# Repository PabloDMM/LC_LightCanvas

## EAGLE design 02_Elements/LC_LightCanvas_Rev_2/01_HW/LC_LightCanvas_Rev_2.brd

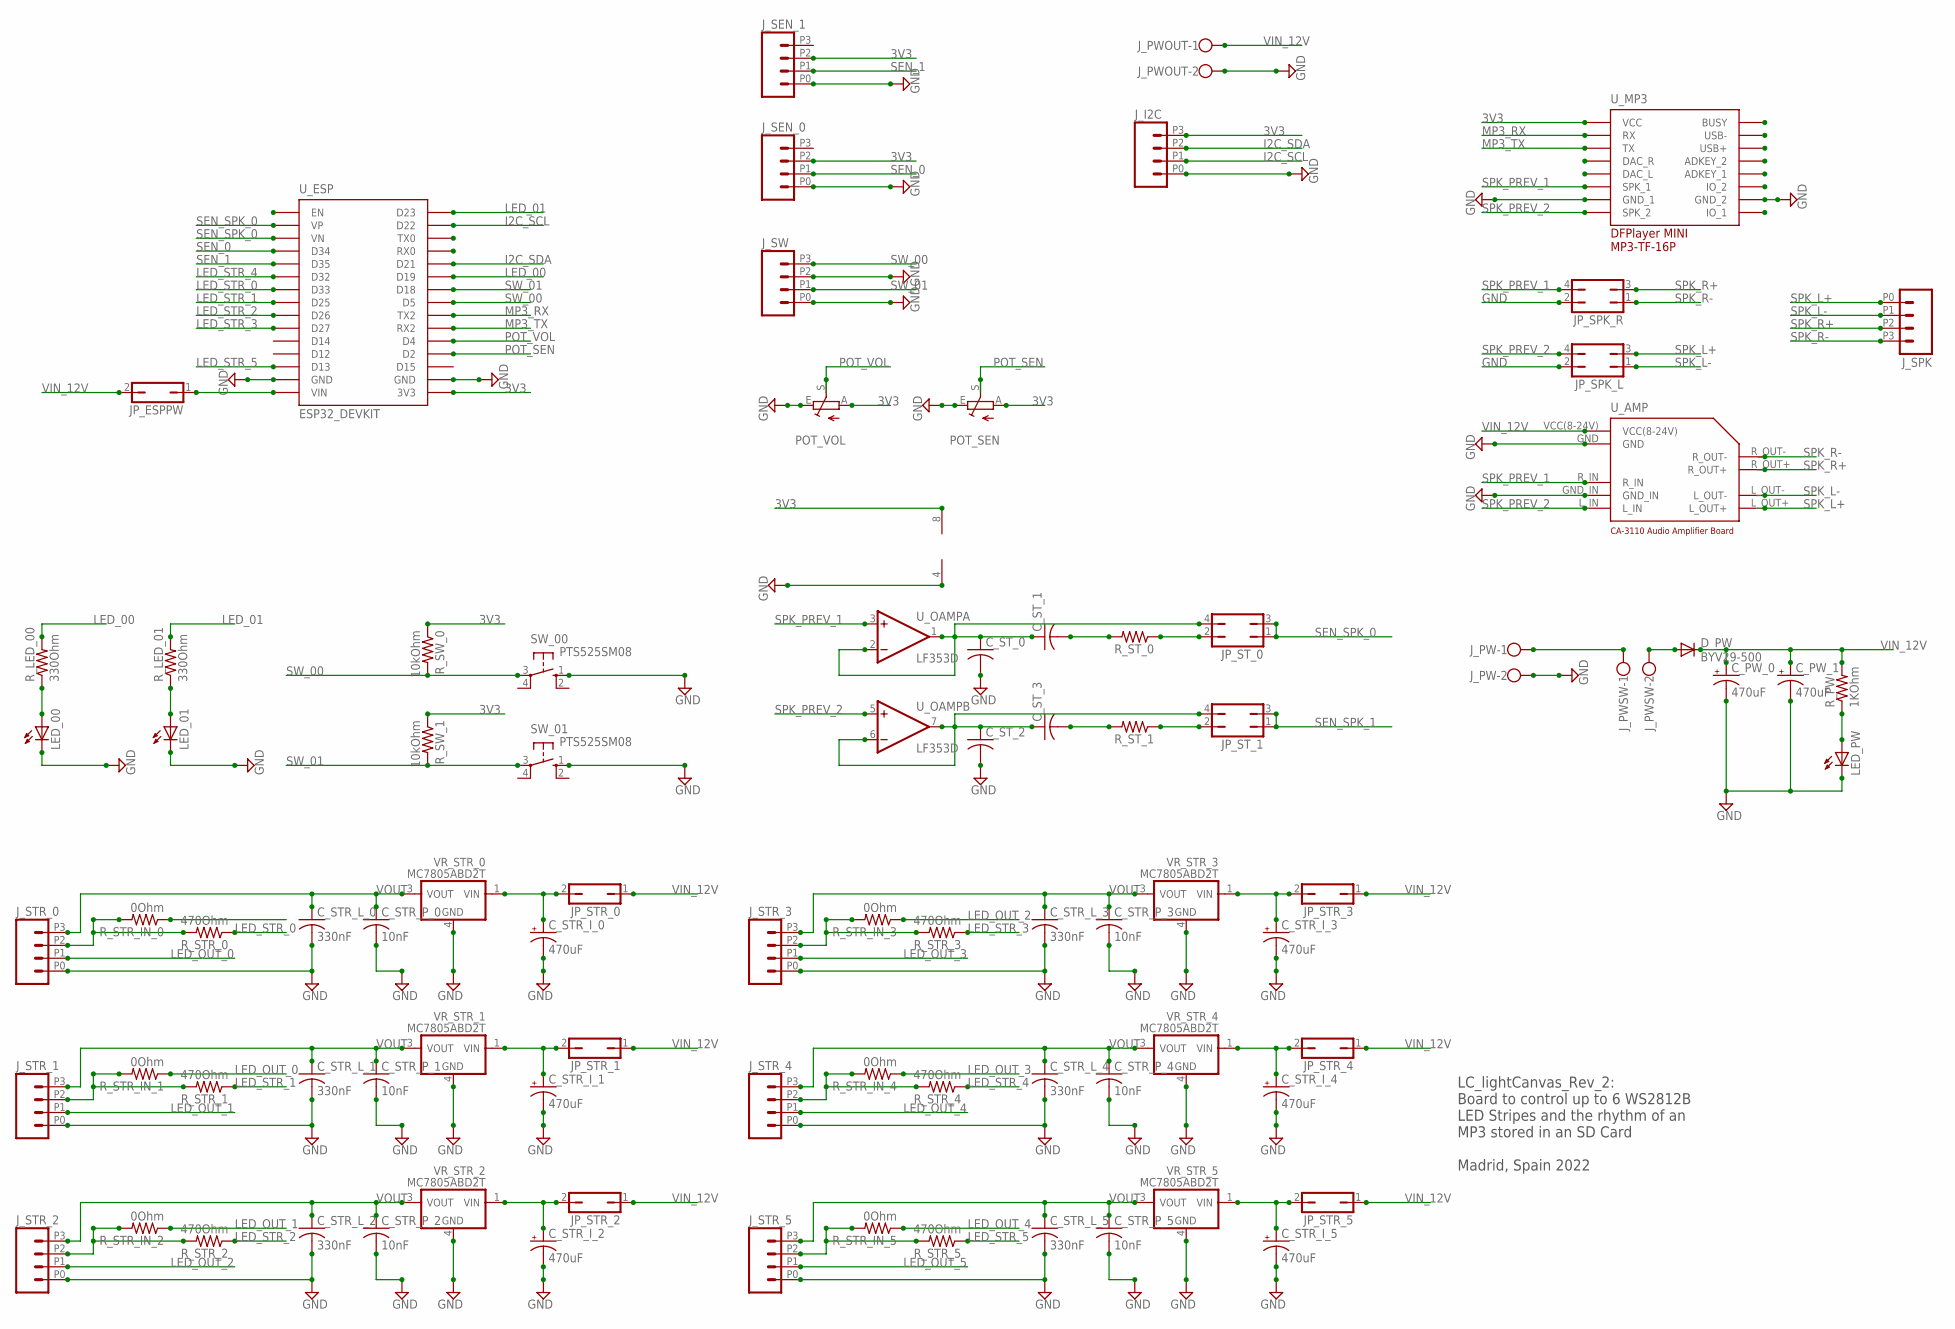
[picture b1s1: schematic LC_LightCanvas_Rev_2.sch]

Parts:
C_PW_0, C_PW_1: 470uF; TT5D10
C_STR_I_0, C_STR_I_1, C_STR_I_2, C_STR_I_3, C_STR_I_4, C_STR_I_5: 470uF; TT5D10
C_STR_L_0, C_STR_L_1, C_STR_L_2, C_STR_L_3, C_STR_L_4, C_STR_L_5: 330nF; C1206
C_STR_P_0, C_STR_P_1, C_STR_P_2, C_STR_P_3, C_STR_P_4, C_STR_P_5: 10nF; C1206
C_ST_0, C_ST_1, C_ST_2, C_ST_3: C-USC1206; C1206
D_PW: BYV29-500; TO220AC
JP_ESPPW: JP1Q; JP1
JP_SPK_L: JP2Q
JP_SPK_R: JP2Q
JP_STR_0, JP_STR_1, JP_STR_2, JP_STR_3, JP_STR_4, JP_STR_5: JP1Q; JP1
JP_ST_0, JP_ST_1: JP2Q
J_I2C: M04; 1X04_2.54_SCREWTERM
J_PW: W237-102
J_PWOUT: W237-102
J_PWSW: W237-102
J_SEN_0, J_SEN_1: M04; 1X04_2.54_SCREWTERM
J_SPK: M04; 1X04_2.54_SCREWTERM
J_STR_0, J_STR_1, J_STR_2, J_STR_3, J_STR_4, J_STR_5: M04; 1X04_2.54_SCREWTERM
J_SW: M04; 1X04_2.54_SCREWTERM
LED_00, LED_01: LEDCHIPLED_1206; CHIPLED_1206
LED_PW: LEDCHIPLED_1206; CHIPLED_1206
POT_SEN: TRIM_EU-CT6; CT6
POT_VOL: TRIM_EU-CT6; CT6
R_LED_00, R_LED_01: 330Ohm; M1206
R_PW: 1KOhm; M1206
R_STR_0, R_STR_1, R_STR_2, R_STR_3, R_STR_4, R_STR_5: 470Ohm; M1206
R_STR_IN_0, R_STR_IN_1, R_STR_IN_2, R_STR_IN_3, R_STR_IN_4, R_STR_IN_5: 0Ohm; M1206
R_ST_0, R_ST_1: R-US_M1206; M1206
R_SW_0, R_SW_1: 10kOhm; M1206
SW_00, SW_01: PTS525SM08; SM08
U_AMP: CA-3110_AUDIOAMPLIFIER
U_ESP: ESP32_DEVKIT
U_MP3: DFPLAYER
U_OAMP: LF353D; SO08
VR_STR_0, VR_STR_1, VR_STR_2, VR_STR_3, VR_STR_4, VR_STR_5: MC7805ABD2T; D2PAK-3

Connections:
3V3: J_I2C.P3 (4), J_SEN_0.P2 (3), J_SEN_1.P2 (3), POT_SEN.A, POT_VOL.A, R_SW_0.1, R_SW_1.1, U_ESP.3V3, U_MP3.VCC, U_OAMP.8 (V+)
GND: C_PW_0.-, C_PW_1.-, C_STR_I_0.-, C_STR_I_1.-, C_STR_I_2.-, C_STR_I_3.-, C_STR_I_4.-, C_STR_I_5.-, C_STR_L_0.2, C_STR_L_1.2, C_STR_L_2.2, C_STR_L_3.2, C_STR_L_4.2, C_STR_L_5.2, C_STR_P_0.2, C_STR_P_1.2, C_STR_P_2.2, C_STR_P_3.2, C_STR_P_4.2, C_STR_P_5.2, C_ST_0.2, C_ST_2.2, JP_SPK_L.2, JP_SPK_R.2, J_I2C.P0 (1), J_PW.2, J_PWOUT.2, J_SEN_0.P0 (1), J_SEN_1.P0 (1), J_STR_0.P0 (1), J_STR_1.P0 (1), J_STR_2.P0 (1), J_STR_3.P0 (1), J_STR_4.P0 (1), J_STR_5.P0 (1), J_SW.P0 (1), J_SW.P2 (3), LED_00.C, LED_01.C, LED_PW.C, POT_SEN.E, POT_VOL.E, SW_00.1 (S), SW_01.1 (S), U_AMP.GND, U_AMP.GND_IN, U_ESP.GND@1 (GND), U_ESP.GND@2 (GND), U_MP3.GND_1, U_MP3.GND_2, U_OAMP.4 (V-), VR_STR_0.4 (GND), VR_STR_1.4 (GND), VR_STR_2.4 (GND), VR_STR_3.4 (GND), VR_STR_4.4 (GND), VR_STR_5.4 (GND)
I2C_SCL: J_I2C.P1 (2), U_ESP.D22
I2C_SDA: J_I2C.P2 (3), U_ESP.D21
LED_00: R_LED_00.2, U_ESP.D19
LED_01: R_LED_01.2, U_ESP.D23
LED_OUT_0: J_STR_0.P1 (2), R_STR_IN_1.1
LED_OUT_1: J_STR_1.P1 (2), R_STR_IN_2.1
LED_OUT_2: J_STR_2.P1 (2), R_STR_IN_3.1
LED_OUT_3: J_STR_3.P1 (2), R_STR_IN_4.1
LED_OUT_4: J_STR_4.P1 (2), R_STR_IN_5.1
LED_OUT_5: J_STR_5.P1 (2)
LED_STR_0: R_STR_0.1, U_ESP.D33
LED_STR_1: R_STR_1.1, U_ESP.D25
LED_STR_2: R_STR_2.1, U_ESP.D26
LED_STR_3: R_STR_3.1, U_ESP.D27
LED_STR_4: R_STR_4.1, U_ESP.D32
LED_STR_5: R_STR_5.1, U_ESP.D13
MP3_RX: U_ESP.TX2, U_MP3.RX
MP3_TX: U_ESP.RX2, U_MP3.TX
unnamed: LED_01.A, R_LED_01.1
unnamed: J_STR_0.P2 (3), R_STR_0.2, R_STR_IN_0.2
unnamed: J_STR_1.P2 (3), R_STR_1.2, R_STR_IN_1.2
unnamed: LED_00.A, R_LED_00.1
unnamed: J_PW.1, J_PWSW.1
unnamed: LED_PW.A, R_PW.1
unnamed: JP_ESPPW.1, U_ESP.VIN
unnamed: J_STR_2.P2 (3), R_STR_2.2, R_STR_IN_2.2
unnamed: J_STR_3.P2 (3), R_STR_3.2, R_STR_IN_3.2
unnamed: C_ST_0.1, C_ST_1.1, JP_ST_0.4, U_OAMP.1 (OUT), U_OAMP.2 (-IN)
unnamed: C_ST_2.1, C_ST_3.1, JP_ST_1.4, U_OAMP.6 (-IN), U_OAMP.7 (OUT)
unnamed: J_STR_4.P2 (3), R_STR_4.2, R_STR_IN_4.2
unnamed: D_PW.A, J_PWSW.2
unnamed: C_ST_1.2, R_ST_0.2
unnamed: J_STR_5.P2 (3), R_STR_5.2, R_STR_IN_5.2
unnamed: JP_ST_0.2, R_ST_0.1
unnamed: C_ST_3.2, R_ST_1.2
unnamed: JP_ST_1.2, R_ST_1.1
POT_SEN: POT_SEN.S, U_ESP.D2
POT_VOL: POT_VOL.S, U_ESP.D4
SEN_0: J_SEN_0.P1 (2), U_ESP.D34
SEN_1: J_SEN_1.P1 (2), U_ESP.D35
SEN_SPK_0: JP_ST_0.1, JP_ST_0.3, U_ESP.VN, U_ESP.VP
SEN_SPK_1: JP_ST_1.1, JP_ST_1.3
SPK_L+: JP_SPK_L.3, J_SPK.P0 (1), U_AMP.L_OUT+
SPK_L-: JP_SPK_L.1, J_SPK.P1 (2), U_AMP.L_OUT-
SPK_PREV_1: JP_SPK_R.4, U_AMP.R_IN, U_MP3.SPK1 (SPK_1), U_OAMP.3 (+IN)
SPK_PREV_2: JP_SPK_L.4, U_AMP.L_IN, U_MP3.SPK2 (SPK_2), U_OAMP.5 (+IN)
SPK_R+: JP_SPK_R.3, J_SPK.P2 (3), U_AMP.R_OUT+
SPK_R-: JP_SPK_R.1, J_SPK.P3 (4), U_AMP.R_OUT-
SW_00: J_SW.P3 (4), R_SW_0.2, SW_00.3, U_ESP.D5
SW_01: J_SW.P1 (2), R_SW_1.2, SW_01.3, U_ESP.D18
VIN_12V: C_PW_0.+, C_PW_1.+, D_PW.C, JP_ESPPW.2, JP_STR_0.1, JP_STR_1.1, JP_STR_2.1, JP_STR_3.1, JP_STR_4.1, JP_STR_5.1, J_PWOUT.1, R_PW.2, U_AMP.VCC(8-24V)
VIN_POS: C_STR_I_0.+, JP_STR_0.2, VR_STR_0.1 (VIN)
VIN_POS1: C_STR_I_1.+, JP_STR_1.2, VR_STR_1.1 (VIN)
VIN_POS2: C_STR_I_2.+, JP_STR_2.2, VR_STR_2.1 (VIN)
VIN_POS3: C_STR_I_3.+, JP_STR_3.2, VR_STR_3.1 (VIN)
VIN_POS4: C_STR_I_4.+, JP_STR_4.2, VR_STR_4.1 (VIN)
VIN_POS5: C_STR_I_5.+, JP_STR_5.2, VR_STR_5.1 (VIN)
VOUT: C_STR_L_0.1, C_STR_L_1.1, C_STR_L_2.1, C_STR_L_3.1, C_STR_L_4.1, C_STR_L_5.1, C_STR_P_0.1, C_STR_P_1.1, C_STR_P_2.1, C_STR_P_3.1, C_STR_P_4.1, C_STR_P_5.1, J_STR_0.P3 (4), J_STR_1.P3 (4), J_STR_2.P3 (4), J_STR_3.P3 (4), J_STR_4.P3 (4), J_STR_5.P3 (4), VR_STR_0.3 (VOUT), VR_STR_1.3 (VOUT), VR_STR_2.3 (VOUT), VR_STR_3.3 (VOUT), VR_STR_4.3 (VOUT), VR_STR_5.3 (VOUT)

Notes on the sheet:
LC_lightCanvas_Rev_2: Board to control up to 6 WS2812B LED Stripes and the rhythm of an MP3 stored in an SD Card Madrid, Spain 2022

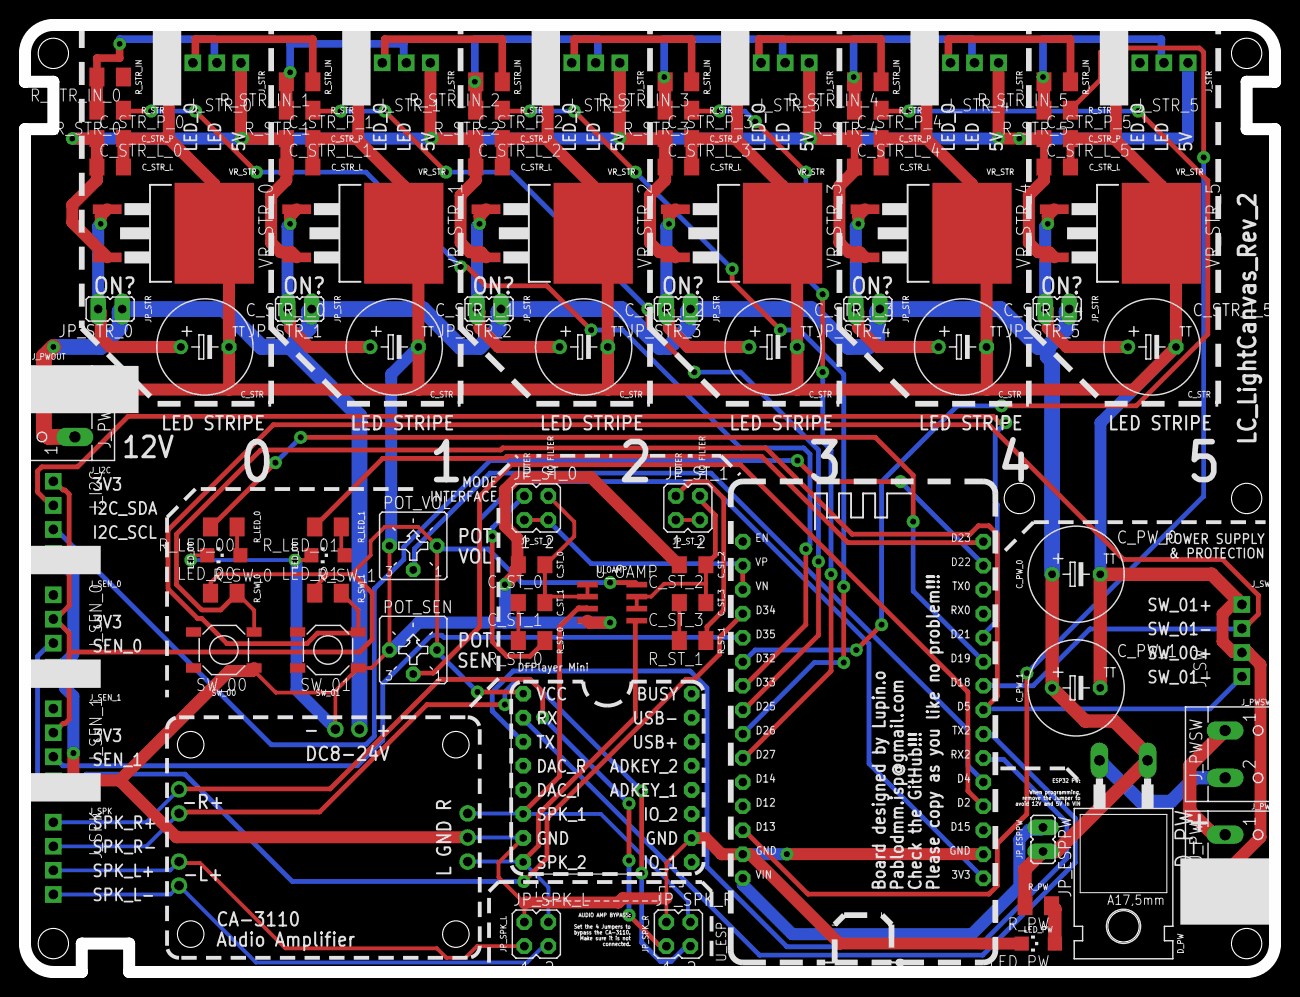
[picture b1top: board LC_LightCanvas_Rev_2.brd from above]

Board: 2 copper layers, 132.0 x 100.0 mm, 86 parts (0 on the bottom side), 59 nets.

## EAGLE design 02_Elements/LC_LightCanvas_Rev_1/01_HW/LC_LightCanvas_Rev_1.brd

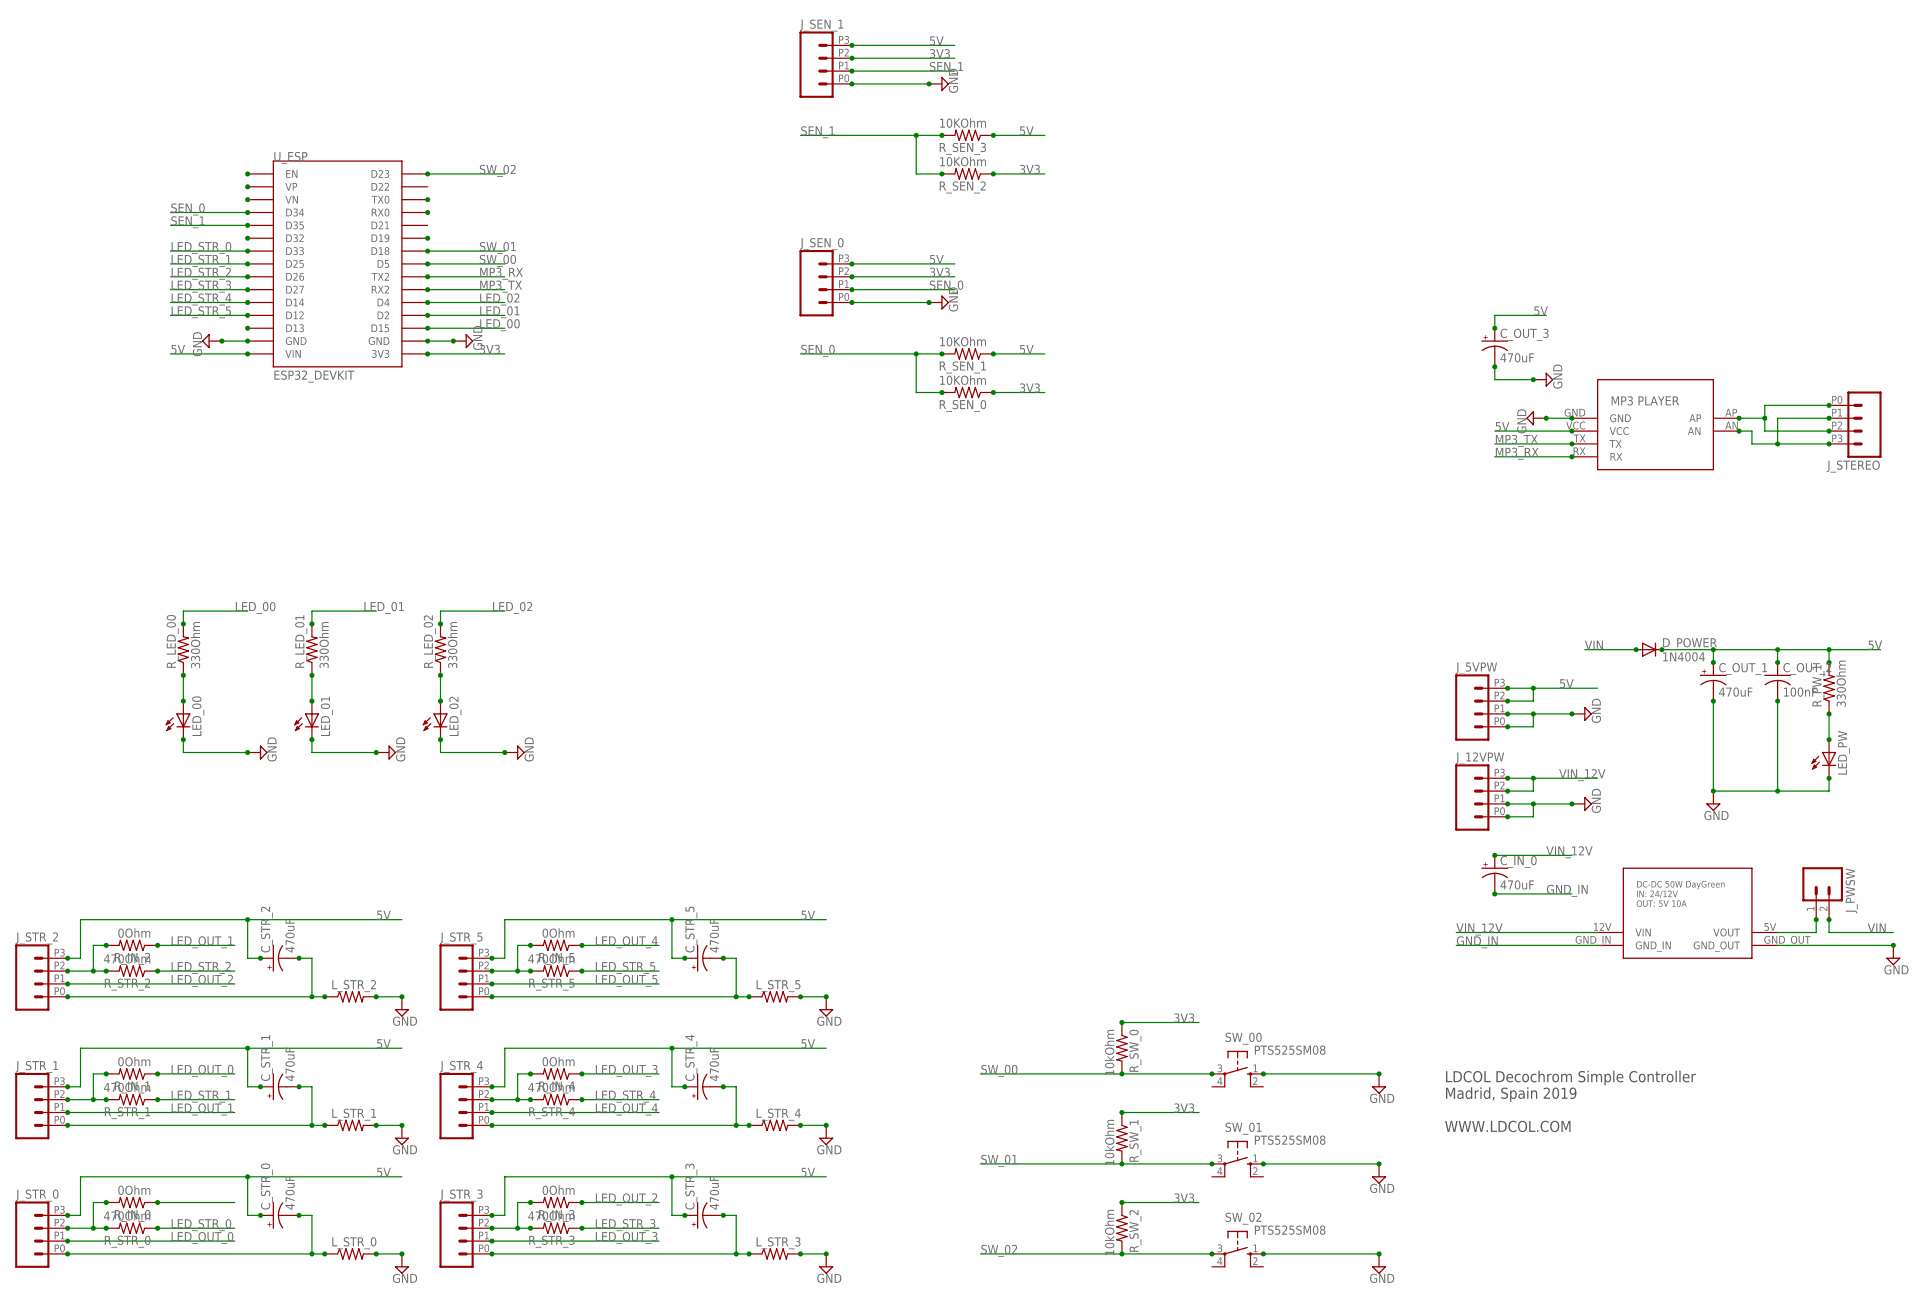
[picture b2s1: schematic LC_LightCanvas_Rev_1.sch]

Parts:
C_IN_0: 470uF; E5-10,5
C_OUT_1, C_OUT_3: 470uF; E5-10,5
C_OUT_2: 100nF; C0805
C_STR_0, C_STR_1, C_STR_2, C_STR_3, C_STR_4, C_STR_5: 470uF; E5-10,5
D_POWER: 1N4004; DO41-10
J_5VPW, J_12VPW: M04; 1X04_2.54_SCREWTERM
J_PWSW: M023.5MM-NO_SILK; SCREWTERMINAL-3.5MM-2-NS
J_SEN_0, J_SEN_1: M04; 1X04_2.54_SCREWTERM
J_STEREO: M04; 1X04_2.54_SCREWTERM
J_STR_0, J_STR_1, J_STR_2, J_STR_3, J_STR_4, J_STR_5: M04; 1X04_2.54_SCREWTERM
LED_00, LED_01, LED_02: LEDCHIPLED_0805; CHIPLED_0805
LED_PW: LEDCHIPLED_0805; CHIPLED_0805
L_STR_0, L_STR_1, L_STR_2, L_STR_3, L_STR_4, L_STR_5: R-US_R2012; R2012
R_IN_0, R_IN_1, R_IN_2, R_IN_3, R_IN_4, R_IN_5: 0Ohm; M0805
R_LED_00, R_LED_01, R_LED_02: 330Ohm; M0805
R_PW_1: 330Ohm; M0805
R_SEN_0, R_SEN_1, R_SEN_2, R_SEN_3: 10KOhm; M1206
R_STR_0, R_STR_1, R_STR_2, R_STR_3, R_STR_4, R_STR_5: 470Ohm; M0805
R_SW_0, R_SW_1, R_SW_2: 10kOhm; M0805
SW_00, SW_01, SW_02: PTS525SM08; SM08
U$1: DC_CONVERTER
U$2: MP3_PLAYER
U_ESP: ESP32_DEVKIT

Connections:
3V3: J_SEN_0.P2 (3), J_SEN_1.P2 (3), R_SEN_0.1, R_SEN_2.1, R_SW_0.1, R_SW_1.1, R_SW_2.1, U_ESP.3V3
5V: C_OUT_1.+, C_OUT_2.1, C_OUT_3.+, C_STR_0.+, C_STR_1.+, C_STR_2.+, C_STR_3.+, C_STR_4.+, C_STR_5.+, D_POWER.C, J_5VPW.P2 (3), J_5VPW.P3 (4), J_SEN_0.P3 (4), J_SEN_1.P3 (4), J_STR_0.P3 (4), J_STR_1.P3 (4), J_STR_2.P3 (4), J_STR_3.P3 (4), J_STR_4.P3 (4), J_STR_5.P3 (4), R_PW_1.2, R_SEN_1.1, R_SEN_3.1, U$2.VCC, U_ESP.VIN
GND: C_OUT_1.-, C_OUT_2.2, C_OUT_3.-, J_5VPW.P0 (1), J_5VPW.P1 (2), J_12VPW.P0 (1), J_12VPW.P1 (2), J_SEN_0.P0 (1), J_SEN_1.P0 (1), LED_00.C, LED_01.C, LED_02.C, LED_PW.C, L_STR_0.2, L_STR_1.2, L_STR_2.2, L_STR_3.2, L_STR_4.2, L_STR_5.2, SW_00.1 (S), SW_01.1 (S), SW_02.1 (S), U$1.GND_OUT, U$2.GND, U_ESP.GND@1 (GND), U_ESP.GND@2 (GND)
GND_IN: C_IN_0.-, U$1.GND_IN
LED_00: R_LED_00.2, U_ESP.D15
LED_01: R_LED_01.2, U_ESP.D2
LED_02: R_LED_02.2, U_ESP.D4
LED_OUT_0: J_STR_0.P1 (2), R_IN_1.1
LED_OUT_1: J_STR_1.P1 (2), R_IN_2.1
LED_OUT_2: J_STR_2.P1 (2), R_IN_3.1
LED_OUT_3: J_STR_3.P1 (2), R_IN_4.1
LED_OUT_4: J_STR_4.P1 (2), R_IN_5.1
LED_OUT_5: J_STR_5.P1 (2)
LED_STR_0: R_STR_0.1, U_ESP.D33
LED_STR_1: R_STR_1.1, U_ESP.D25
LED_STR_2: R_STR_2.1, U_ESP.D26
LED_STR_3: R_STR_3.1, U_ESP.D27
LED_STR_4: R_STR_4.1, U_ESP.D14
LED_STR_5: R_STR_5.1, U_ESP.D12
MP3_RX: U$2.RX, U_ESP.TX2
MP3_TX: U$2.TX, U_ESP.RX2
unnamed: LED_01.A, R_LED_01.1
unnamed: LED_02.A, R_LED_02.1
unnamed: C_STR_0.-, J_STR_0.P0 (1), L_STR_0.1
unnamed: C_STR_1.-, J_STR_1.P0 (1), L_STR_1.1
unnamed: J_STR_1.P2 (3), R_IN_1.2, R_STR_1.2
unnamed: LED_00.A, R_LED_00.1
unnamed: J_PWSW.1, U$1.5V (VOUT)
unnamed: LED_PW.A, R_PW_1.1
unnamed: J_STR_0.P2 (3), R_IN_0.2, R_STR_0.2
unnamed: C_STR_3.-, J_STR_3.P0 (1), L_STR_3.1
unnamed: C_STR_2.-, J_STR_2.P0 (1), L_STR_2.1
unnamed: J_STR_2.P2 (3), R_IN_2.2, R_STR_2.2
unnamed: J_STR_3.P2 (3), R_IN_3.2, R_STR_3.2
unnamed: C_STR_4.-, J_STR_4.P0 (1), L_STR_4.1
unnamed: J_STR_4.P2 (3), R_IN_4.2, R_STR_4.2
unnamed: C_STR_5.-, J_STR_5.P0 (1), L_STR_5.1
unnamed: J_STR_5.P2 (3), R_IN_5.2, R_STR_5.2
unnamed: J_STEREO.P0 (1), J_STEREO.P2 (3), U$2.AP
unnamed: J_STEREO.P1 (2), J_STEREO.P3 (4), U$2.AN
SEN_0: J_SEN_0.P1 (2), R_SEN_0.2, R_SEN_1.2, U_ESP.D34
SEN_1: J_SEN_1.P1 (2), R_SEN_2.2, R_SEN_3.2, U_ESP.D35
SW_00: R_SW_0.2, SW_00.3, U_ESP.D5
SW_01: R_SW_1.2, SW_01.3, U_ESP.D18
SW_02: R_SW_2.2, SW_02.3, U_ESP.D23
VIN: D_POWER.A, J_PWSW.2
VIN_12V: C_IN_0.+, J_12VPW.P2 (3), J_12VPW.P3 (4), U$1.12V (VIN)

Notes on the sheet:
LDCOL Decochrom Simple Controller Madrid, Spain 2019 WWW.LDCOL.COM

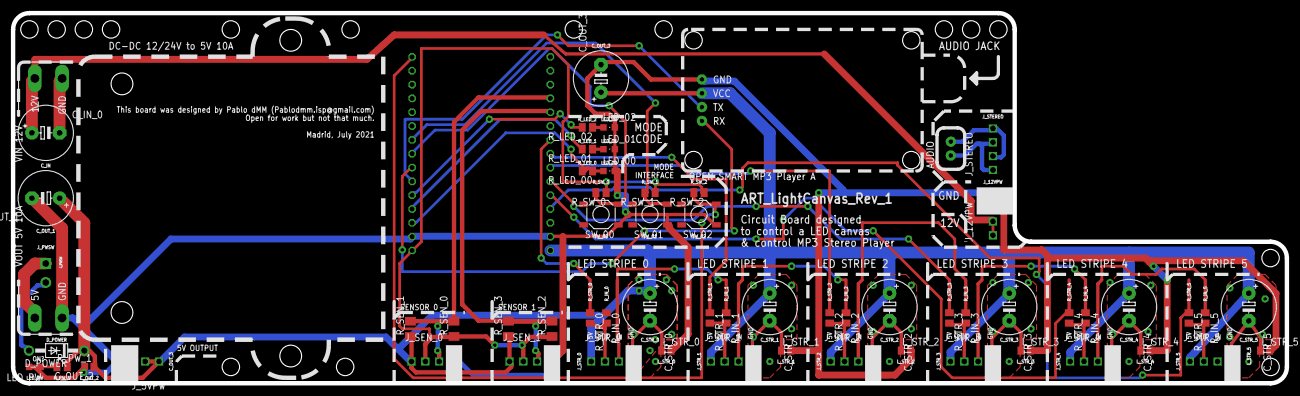
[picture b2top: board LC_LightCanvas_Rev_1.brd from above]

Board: 2 copper layers, 234.0 x 68.0 mm, 62 parts (1 on the bottom side), 46 nets.

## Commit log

2022-08-26 First Commit
    - Inheritance from repository ART_Collage
    - First upload of LC_LightCanvas_Rev_2
2022-08-26 Fix of HW and Gerber Files
    Fixed HW
    Generation of Gerber Files
    Generation of 3D Model
2022-08-27 Added LC_LightCanvar_Rev_2_BOM.txt Only with the PPCB parts.
2022-10-06 Updated Code with the Extra controls
2022-10-21 Update with first Milestone hit
2022-10-23 Uploaded Documentaion of LC_LightCanvas_Rev_2
2022-10-29 Updated a new Image of the correction to H4_MainController_Rev_1 board

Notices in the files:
02_Elements/LC_LightCanvas_Rev_1/01_HW/LC_LightCanvas_Rev_1.sch:
CC BY-SA 2.0
parts and their libraries:
SparkFun-Connectors2: Licensing: Creative Commons ShareAlike 4.0 International - https://creativecommons.org/licenses/by-sa/4.0
